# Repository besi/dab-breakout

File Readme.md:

# DAB Breakout board

## Flash chip

Optionally a SST2VF016B-50-4C-S2AF Flash chip can be populated.

## Credits

- [3D model of the headphone jack](https://grabcad.com/library/3-5mm-audio-jack-1) by [Bilal](https://grabcad.com/bilal-72)

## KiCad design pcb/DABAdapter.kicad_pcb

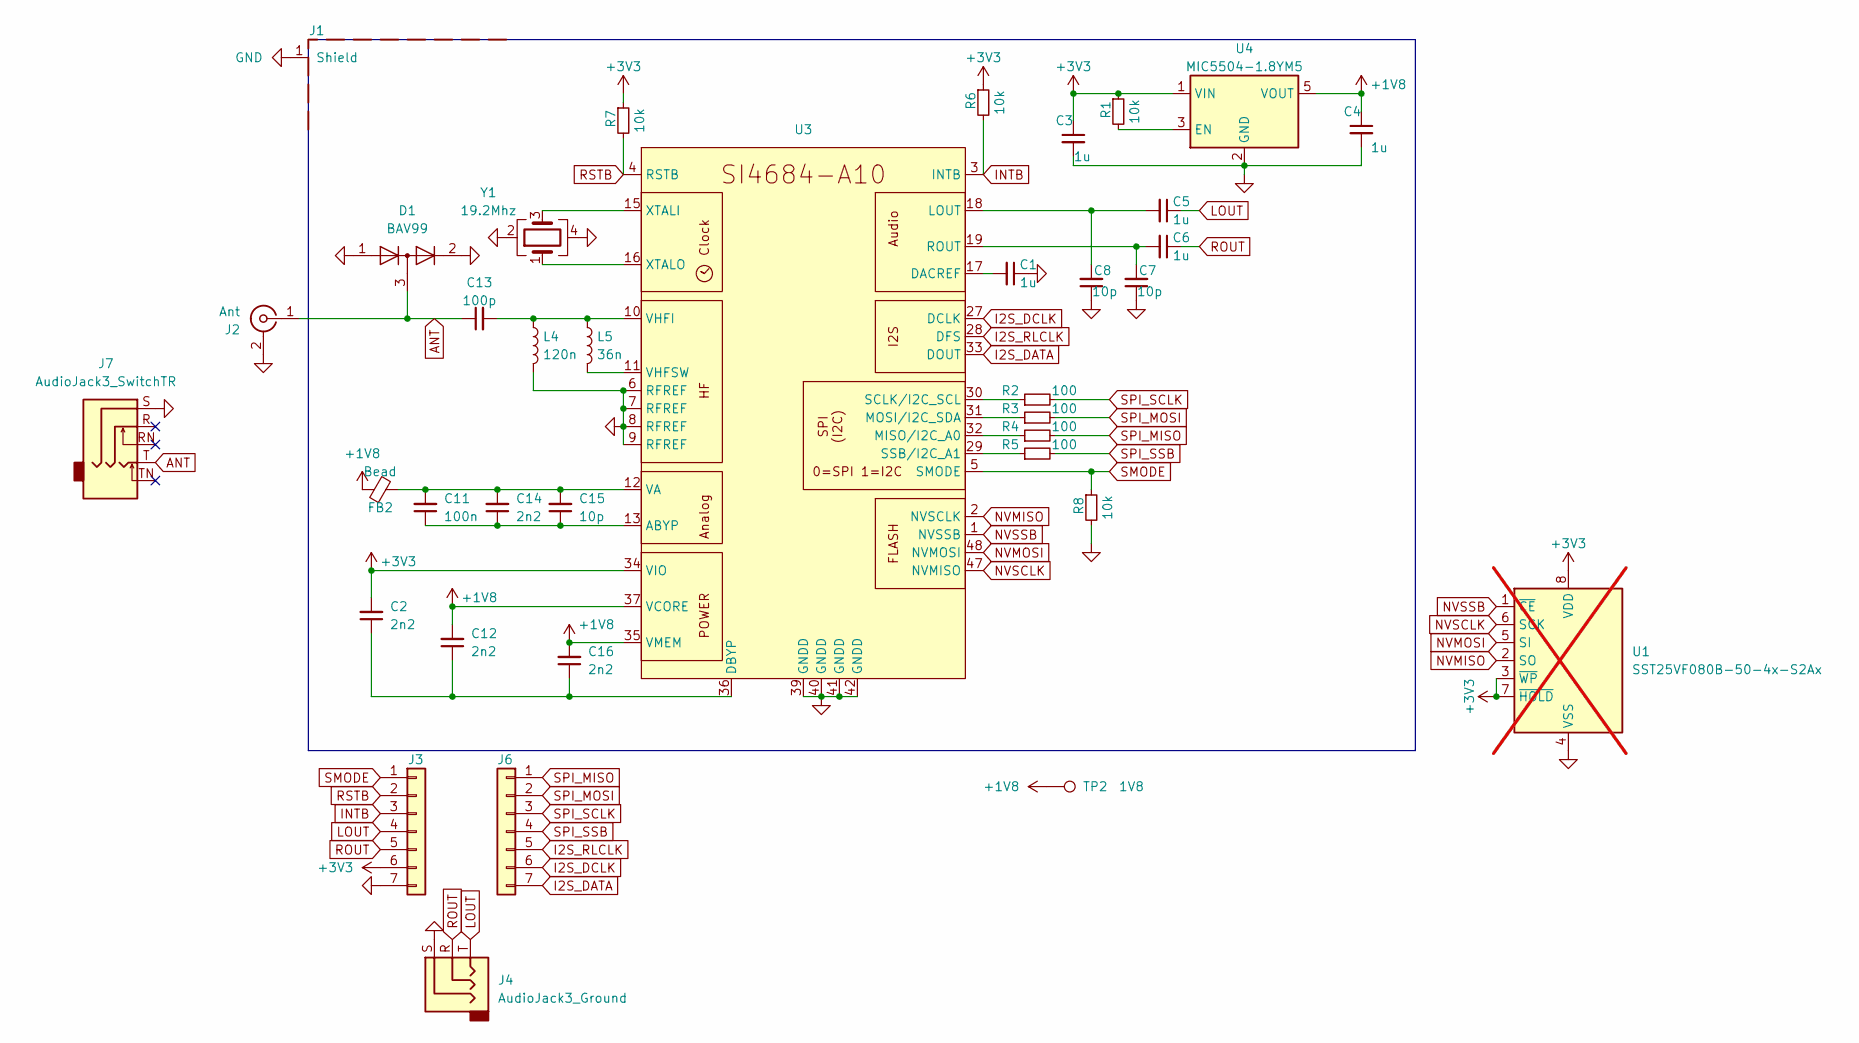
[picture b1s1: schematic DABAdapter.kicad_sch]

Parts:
C1, C3, C4, C5, C6: 1u; C0402; LCSC C52923
C2, C12, C14, C16: 2n2; C0603; LCSC C1604
C7, C8, C15: 10p; C0402; LCSC C32949
C11: 100n; C0402; LCSC C1525
C13: 100p; C0402; LCSC C1546
D1: BAV99; SOT-23-3_L2.9-W1.3-P1.90-LS2.4-BR; LCSC C916421
FB2: Bead; L0603; LCSC C1002
J1: RFShield_OnePiece; Wuerth_36103255_25x25mm
J2: Ant; SMA_Amphenol_132134-16_Vertical
J3, J6: Conn_01x06; PinHeader_1x07_P2.54mm_Vertical
J4: AudioJack3_Ground; Jack_3.5mm_CUI_SJ-3524-SMT_Horizontal
J7: AudioJack3_SwitchTR; Jack_3.5mm_CUI_SJ2-3593D-SMT_Horizontal
L4: 120n; L0402; LCSC C27149
L5: 36n; L0402; LCSC C74296
R1, R6, R7, R8: 10k; C0402; LCSC C25744
R2, R3, R4, R5: 100; C0402; LCSC C25076
TP2: 1V8; TestPoint_Pad_D1.0mm
U1: SST25VF080B-50-4x-S2Ax; SOIC-8_5.275x5.275mm_P1.27mm; not fitted
U3: abcdefg; QFN-48-1EP_7x7mm_P0.5mm_EP5.3x5.3mm; LCSC C2654613
U4: MIC5504-1.8YM5; TSOT-23-5_L2.9-W1.6-P0.95-LS2.8-BR; LCSC C626116
Y1: 19.2Mhz; CRYSTAL-SMD_4P-L3.2-W2.5-BL; LCSC C479197

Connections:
+1V8: C4.1, C12.2, C16.2, FB2.1, TP2.1, U3.35 (VMEM), U3.37 (VCORE), U4.5 (VOUT)
+3V3: C2.2, C3.1, J3.6, R1.1, R6.1, R7.1, U1.3 (~WP), U1.7 (~HOLD), U1.8 (VDD), U3.34 (VIO), U4.1 (VIN)
ANT: C13.1, D1.3 (K), J2.1 (In), J7.T
GND: C1.1, C3.2, C4.2, C7.1, C8.1, D1.1 (K), D1.2 (A), J1.1 (Shield), J2.2 (Ext), J3.7, J4.S, J7.S, L4.2, R8.2, U1.4 (VSS), U3.6 (RFREF), U3.7 (RFREF), U3.8 (RFREF), U3.9 (RFREF), U3.39 (GNDD), U3.40 (GNDD), U3.41 (GNDD), U3.42 (GNDD), U4.2 (GND), Y1.2, Y1.4
I2S_DATA: J6.7, U3.33 (DOUT)
I2S_DCLK: J6.6, U3.27 (DCLK)
I2S_RLCLK: J6.5, U3.28 (DFS)
INTB: J3.3, R6.2, U3.3 (INTB)
LOUT: C5.1, J3.4, J4.T
NVMISO: U1.2 (SO), U3.2 (NVSCLK)
NVMOSI: U1.5 (SI), U3.48 (NVMOSI)
NVSCLK: U1.6 (SCK), U3.47 (NVMISO)
NVSSB: U1.1 (~CE), U3.1 (NVSSB)
unnamed: C11.1, C14.1, C15.1, U3.13 (ABYP)
unnamed: C1.2, U3.17 (DACREF)
unnamed: C2.1, C12.1, C16.1, U3.36 (DBYP)
unnamed: C5.2, C8.2, U3.18 (LOUT)
unnamed: R4.1, U3.32 (MISO/I2C_A0)
unnamed: R3.1, U3.31 (MOSI/I2C_SDA)
unnamed: C6.2, C7.2, U3.19 (ROUT)
unnamed: R2.1, U3.30 (SCLK/I2C_SCL)
unnamed: R5.1, U3.29 (SSB/I2C_A1)
unnamed: C11.2, C14.2, C15.2, FB2.2, U3.12 (VA)
unnamed: C13.2, L4.1, L5.1, U3.10 (VHFI)
unnamed: L5.2, U3.11 (VHFSW)
unnamed: U3.15 (XTALI), Y1.3
unnamed: U3.16 (XTALO), Y1.1
unnamed: R1.2, U4.3 (EN)
ROUT: C6.1, J3.5, J4.R
RSTB: J3.2, R7.2, U3.4 (RSTB)
SMODE: J3.1, R8.1, U3.5 (SMODE)
SPI_MISO: J6.1, R4.2
SPI_MOSI: J6.2, R3.2
SPI_SCLK: J6.3, R2.2
SPI_SSB: J6.4, R5.2

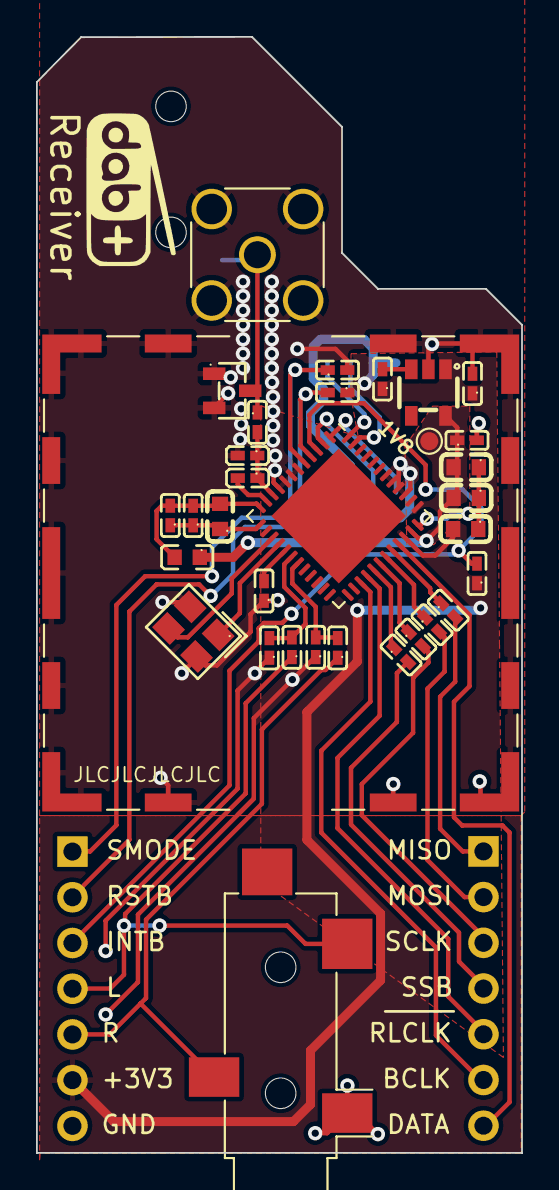
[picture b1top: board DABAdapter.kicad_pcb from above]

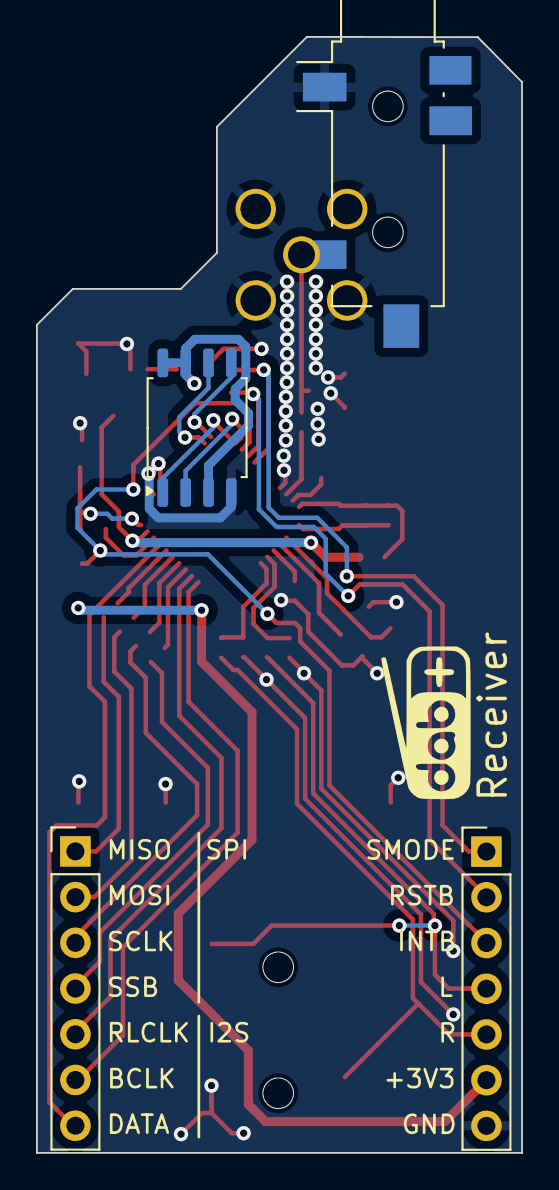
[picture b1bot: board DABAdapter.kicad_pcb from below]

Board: 2 copper layers, 27.0 x 62.0 mm, 37 parts (4 on the bottom side), 35 nets.

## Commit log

2025-01-30 Add schematic and initial pcb
2025-03-01 Add credits to the readme
2025-03-01 Add flash chip to the layout
2026-01-16 Routing of the pcb
2026-01-16 DRC and add step file of QFN package
2026-01-16 Rename FS to RLCLK
2026-01-17 Finishing touches
    - Added image to readme
    - Add Wuerth 3d model of the shield
    - Add DAB logo to the pcb
    - New board outline for the optional TRS antenna socket
